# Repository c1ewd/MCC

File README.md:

# Microclimate controller (MCC)

> Project based STM32F030K6T6

## Dependensies

- CMSIS

## Clone

> Clone this repo to your local machine using `git clone https://github.com/c1ewd/MCC`

## Features

> Device intended for measuring humidity and temperature. By deviation from specified range of temperature or humidity it send sound signal.
> Hardware design was making in Eagle CAD. Software was coding in IAR.
> Device is using digital humidity and temperature sensor AM2302. For sound signal using EFM-475. For graphical interface using Nokia 5110 display.

## Donations (Optional)

## License

- **[MIT license](http://opensource.org/licenses/mit-license.php)**
- Copyright © 2020 <a href="https://teleg.run/c1ewd" target="_blank">c1ewd</a>.

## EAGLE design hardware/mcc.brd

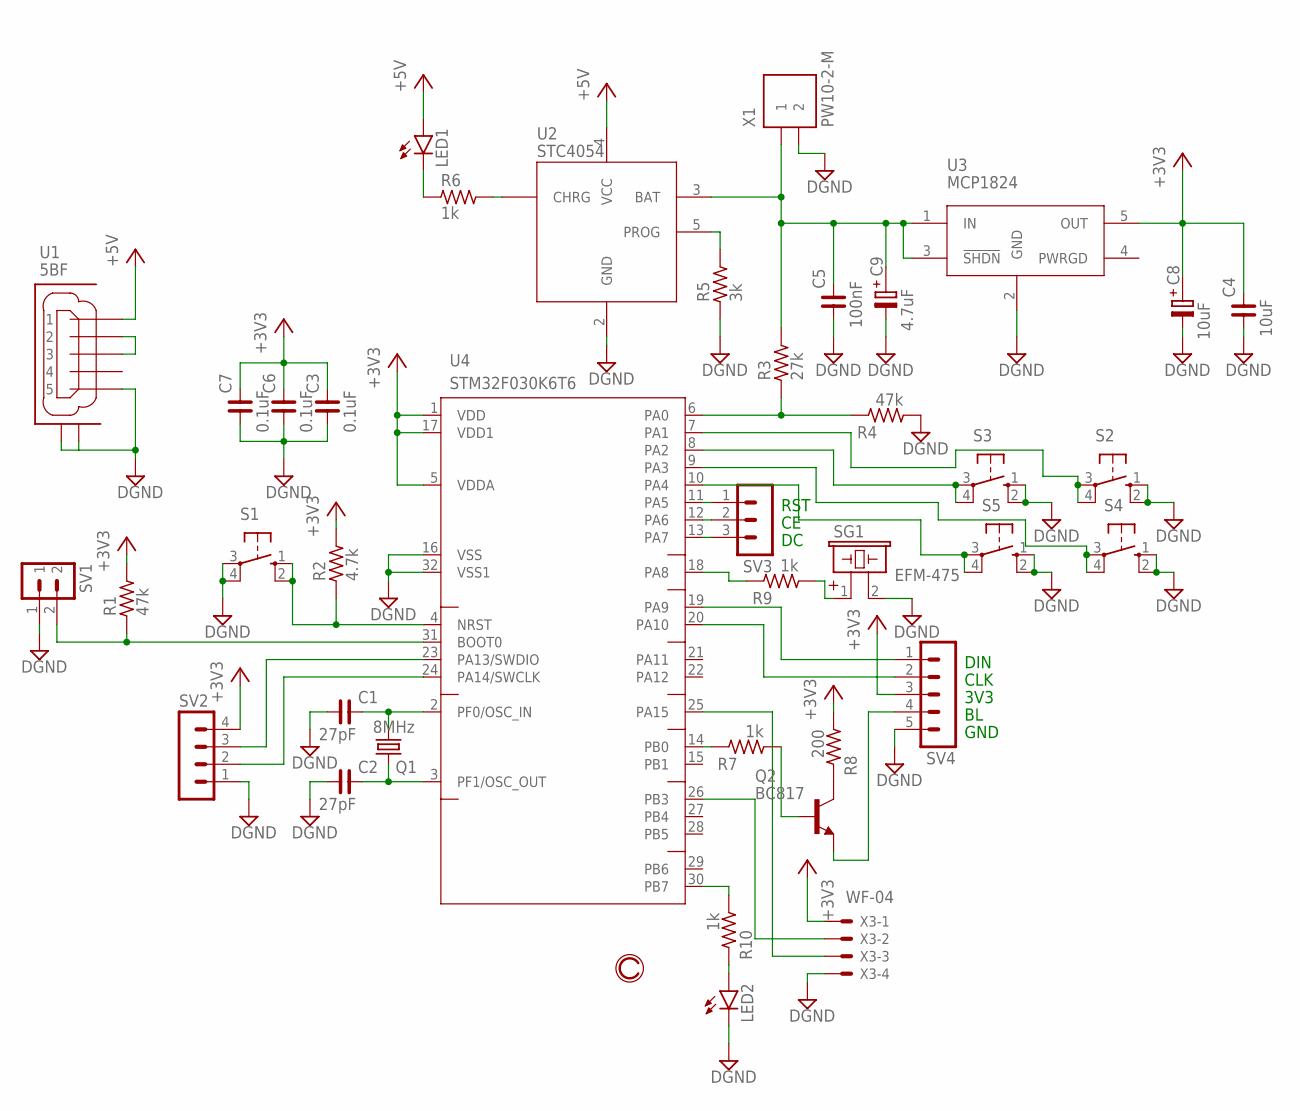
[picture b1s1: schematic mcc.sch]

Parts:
C1, C2: 27pF; C0805
C3, C6, C7: 0.1uF; C0805
C4: 10uF; C1206
C5: 100nF; C0805
C8: 10uF; SV-C
C9: 4.7uF; SV-C
LED1, LED2: LEDSML0805; SML0805
Q1: 8MHz; HC49UP
Q2: BC817; SOT23-BEC
R1, R4: 47k; R0805
R2: 4.7k; R0805
R3: 27k; R0805
R5: 3k; R0805
R6, R7, R9, R10: 1k; R0805
R8: 200; R0805
S1, S2, S3, S4, S5: 10-XX; B3F-10XX
SG1: EFM-475; EFM-472
SV1: MA02-1
SV2: MA04-1
SV3: MA03-1
SV4: MA05-1
U1: 5BF; MICRO-USB-5BF
U2: STC4054; SOT23-5L
U3: MCP1824; SOT23-5L
U4: STM32F030K6T6; LQFP-32
X1: PW10-2-M; MKS1852-6-0-202
X3: WF-04; 22-23-2041

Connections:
+3V3: C3.2, C4.2, C6.2, C7.2, C8.+, R1.2, R2.2, R8.1, SV2.4, SV4.3, U3.5 (OUT), U4.1 (VDD), U4.5 (VDDA), U4.17 (VDD1), X3.1
BAT: C5.2, C9.+, R3.2, U2.3 (BAT), U3.1 (IN), U3.3 (!SHDN), X1.1
BL: R7.2, U4.14 (PB0)
BOOT0: R1.1, SV1.2, U4.31 (BOOT0)
BUZZER: R9.2, U4.18 (PA8)
CE: SV3.2, U4.12 (PA6)
CHRG: R6.2, U2.1 (CHRG)
CLK: SV4.2, U4.20 (PA10)
DATA: U4.26 (PB3), X3.2
DC: SV3.3, U4.13 (PA7)
DGND: C1.1, C2.1, C3.1, C4.1, C5.1, C6.1, C7.1, C8.-, C9.-, LED2.C, R4.1, R5.1, S1.3, S1.4 (P1), S2.1 (S), S2.2 (S1), S3.1 (S), S3.2 (S1), S4.1 (S), S4.2 (S1), S5.1 (S), S5.2 (S1), SG1.2, SV1.1, SV2.1, SV4.5, U1.5, U1.GND1, U1.GND2, U2.2 (GND), U3.2 (GND), U4.16 (VSS), U4.32 (VSS1), X1.2, X3.4
DIN: SV4.1, U4.19 (PA9)
DIV_BAT: R3.1, R4.2, U4.6 (PA0)
LED2: R10.1, U4.30 (PB7)
unnamed: U4.25 (PA15), X3.3
unnamed: U1.2, U1.3
NRST: R2.1, S1.1 (S), S1.2 (S1), U4.4 (NRST)
PF0-OSC_IN: C1.2, Q1.1, U4.2 (PF0/OSC_IN)
PF1-OSC_OUT: C2.2, Q1.2, U4.3 (PF1/OSC_OUT)
PROG: R5.2, U2.5 (PROG)
RST: SV3.1, U4.11 (PA5)
R_+3V3: Q2.C, R8.2
R_BL: Q2.B, R7.1
R_BUZZER: R9.1, SG1.1
R_CHRG: LED1.C, R6.1
R_LED2: LED2.A, R10.2
S2: S2.3, S2.4 (P1), U4.7 (PA1)
S3: S3.3, S3.4 (P1), U4.8 (PA2)
S4: S4.3, S4.4 (P1), U4.9 (PA3)
S5: S5.3, S5.4 (P1), U4.10 (PA4)
SWCLK: SV2.2, U4.24 (PA14/SWCLK)
SWDIO: SV2.3, U4.23 (PA13/SWDIO)
VCC: LED1.A, U1.1, U2.4 (VCC)
Е_BL: Q2.E, SV4.4

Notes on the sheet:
RST
DIN
CLK
3V3
GND

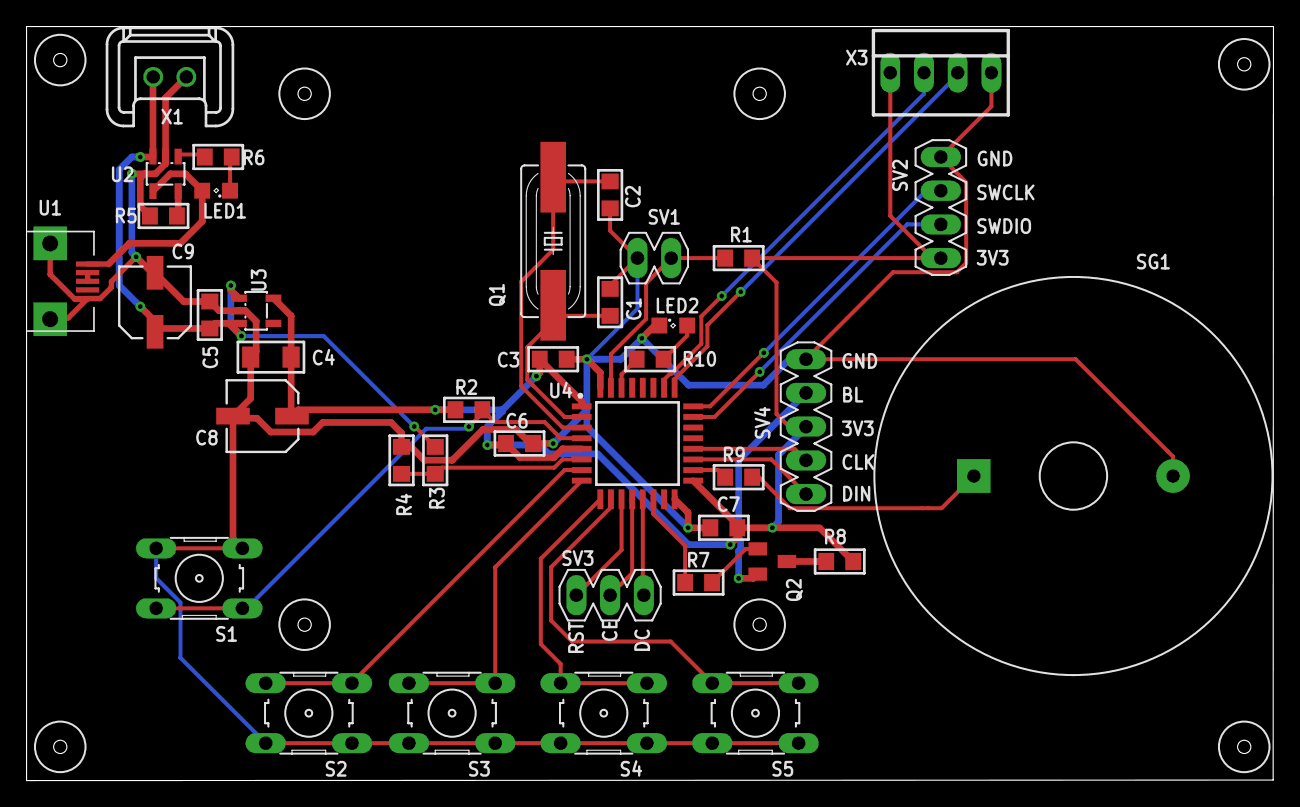
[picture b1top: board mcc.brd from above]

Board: 2 copper layers, 94.0 x 56.8 mm, 39 parts (0 on the bottom side), 34 nets.

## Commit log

2020-08-01 Was added README.md
2020-08-01 Was added .gitignore
2020-08-01 Was added hardware design
2020-08-01 Was updated README.md

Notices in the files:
hardware/mcc.brd:
© C1ewd
parts and their libraries:
rc-master-smd: Copyright (C) 2007, Bob Starr
